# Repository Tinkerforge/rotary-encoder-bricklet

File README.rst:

Rotary Encoder Bricklet
=======================

This repository contains the firmware source code and the hardware design
files. The documentation generator configs can be found at
https://github.com/Tinkerforge/generators

Repository Content
------------------

software/:
 * examples/: Examples for all supported languages
 * build/: Compiled files
 * src/: Source code of firmware
 * Makefile: Makefile to build project

hardware/:
 * Contains KiCad project files and additionally schematics as PDF

datasheets/:
 * Contains datasheets for sensors and complex ICs that are used

Hardware
--------

The hardware is designed with the open source EDA Suite KiCad
(http://www.kicad.org). Before you are able to open the files,
you have to install the Tinkerforge kicad-libraries
(https://github.com/Tinkerforge/kicad-libraries). You can either clone
them directly in hardware/ or clone them in a separate folder and
symlink them into hardware/
(ln -s kicad_path/kicad-libraries project_path/hardware). After that you
can open the .pro file in hardware/ with KiCad and from there view and
modify the schematics and the PCB layout.

Software
--------

If you want to do your own Brick/Bricklet firmware development we highly
recommend that you use our build environment setup script and read the
tutorial (https://www.tinkerforge.com/en/doc/Tutorials/Tutorial_Build_Environment/Tutorial.html).

To compile the C code we recommend you to install the newest GNU Arm Embedded
Toolchain (https://launchpad.net/gcc-arm-embedded/+download).
You also need to install bricklib (https://github.com/Tinkerforge/bricklib)
and brickletlib (https://github.com/Tinkerforge/brickletlib).

You can either clone it directly in software/src/ or clone it in a
separate folder and symlink it into software/src/
(ln -s bricklib_path/bricklib project_path/software/src/ and
ln -s brickletlib_path/brickletlib project_path/software/src/).
Finally make sure to have CMake installed
(http://www.cmake.org/cmake/resources/software.html).

After that you can build the firmware by invoking make in software/.
The firmware (.bin) can then be found in software/build/ and uploaded
with brickv (click button "Flashing" on start screen).

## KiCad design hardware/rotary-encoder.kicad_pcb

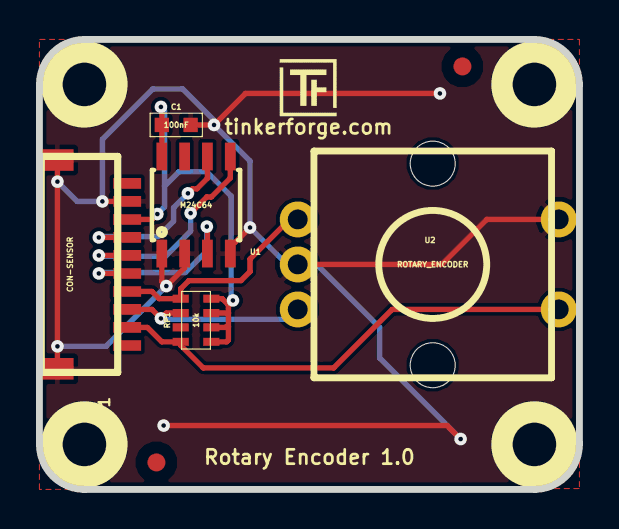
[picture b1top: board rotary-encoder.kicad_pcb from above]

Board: 2 copper layers, 30.0 x 25.0 mm, 13 parts (0 on the bottom side), 8 nets.

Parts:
C1: 100nF; 0603
Fiducial_Mark: VAL**; Fiducial_Mark
Fiducial_Mark#2: VAL**; Fiducial_Mark
P1: CON-SENSOR
RP1: 10k; 4X0603
U1: M24C64; SOIC8
U2: ROTARY_ENCODER
U3, U4, U5, U6: DRILL; DRILL_NP
VAL: WEEE_7mm
VAL#2: CE_5mm

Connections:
GND: C1.2, P1.2, P1.EP, U1.1, U1.2, U1.4, U2.C, U2.SW2
unnamed: P1.6, U1.3
unnamed: P1.9, RP1.1, U2.SW1
unnamed: P1.8, RP1.3, U2.B
unnamed: P1.7, RP1.4, U2.A
unnamed: P1.4, U1.6
unnamed: P1.5, U1.5
VCC: C1.1, P1.3, RP1.5, RP1.6, RP1.7, RP1.8, U1.8

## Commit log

2013-08-20 Initial commit of Rotary Encoder Bricklet (actual counting still missing in firmware)
2013-08-20 Add count reset functionality
2013-08-21 Add count calculation API for button pressed/released
2013-08-21 Add encoder datasheet
2013-08-21 windows: Don't trigger a build in generate_makefile.bat
    Also use normal make instead of a special named one.
2013-09-13 Add examples for Rotary Encoder Bricklet
2013-09-13 Fix variable name
2013-09-13 Fix variable name in java examples
2013-10-15 add hardware files
2013-10-18 Fix name to fit naming convention
2013-12-19 Fix wrong length for GetDebounce packet (through brickletlib)
2014-01-06 Add static assert for BrickContext size
2014-01-10 Add Perl examples
2014-01-15 php: Use const for constant values
2014-02-07 Add Mathematica examples
2014-02-10 perl: fixed namespace
2014-02-11 javascript: add examples
2014-02-18 javascript: examples fixed
2014-02-20 javascript: add html examples
2014-02-24 javascript: port 4280, startExample()
2014-02-28 javascript: Break long lines and cleanup whitespace
2014-03-05 Fix typo
2014-03-05 Add LabVIEW examples
2014-03-06 labview: Add examples in LV2010 format
2014-03-27 matlab: add examples
2014-03-28 perl: Fix warning
2014-04-02 java: Unify constants style
2014-04-02 perl: Unify print style
2014-04-17 matlab: Adapt examples to new callback style
2014-04-17 matlab: Add parentheses to make pygments happy
2014-07-15 java: Replace System.console() usage with an Eclipse compatible pattern
2014-12-02 Use ReadLine instead of ReadKey for C# example
2015-02-13 vbnet: Use ReadLine instead of ReadKey
    Because ReadKey doesn't work with a pipe as stdin on the RED Brick.
2015-03-02 windows: Stop cmake from searching for mingw32-make.exe
    Using MinGW Makefiles as generator makes cmake search for mingw32-make.exe
    which might not be installed because GnuWin32's make.exe is used instead.
2015-04-09 c: Whitespace
2015-06-24 javascript: Clean up output creation
2015-07-25 Make JavaScript browser example textarea readonly
2015-07-27 Cleanup C/C++, C#, Java, Python and Ruby examples
2015-07-28 Whitespace
2015-07-29 Reformat changelog
2015-07-30 Unify comments in examples
2015-08-07 Use full device class name in Python examples
2015-08-12 Fix minor warnings in C/C++ examples
2015-08-14 Cleanup Delphi examples
2015-08-18 Cleanup VB.NET examples
2015-08-19 Cleanup Perl examples
2015-08-21 Use shorter print statement in Perl example
2015-09-09 Duplicate cmake call to fix bug during cmake creation
2015-09-30 Generator based example cleanup
2015-11-12 matlab: Fix callback handling for R2014a
    http://undocumentedmatlab.com/blog/matlab-callbacks-for-java-events-in-r2014a
2015-11-25 Include date and commit into changelog
2016-04-25 Fix inverted is_pressed return value
2016-04-25 Add changelog commit after the fact
2016-05-18 c: Add missing device destroy call
2016-07-01 Make the change UID comment more explicit
2017-04-13 csharp: Adapt example
2017-06-02 octave: Use javaObject instead of deprecated java_new
2017-11-30 Update examples from generator
2017-12-07 mathematica: Also generate .nb files
2018-02-19 javascript: Close div tag correctly
2018-02-20 Cleanup KiCad libraries config
    Ensure LibDir=kicad-libraries and LibName1=tinkerforge.
    Remove special library.
2018-05-11 Rename files
2018-05-24 perl: Use strict in examples
2018-07-11 Add Makefile with docker support
2018-07-11 Remove obsolete generate_makefile scripts
2018-07-11 Update directory structure and build instructions
2018-11-06 Add rust examples
2018-11-07 rust: Accept host names for ip connection, fix naming inconsistencies
2018-11-07 rust: Rename callback receivers.
2018-12-14 Add go examples.
2018-12-18 go: Change import path.
2018-12-18 go: Change import path again.
2018-12-20 rust: Reformat examples.
2019-01-24 mqtt: Add examples.
2019-01-24 mqtt: Fix example header.
2019-01-24 mqtt: Remove executable bit in example permissions.
2019-01-24 go: Minor example fixes.
2019-01-24 mqtt: Minor example fixes.
2019-03-25 mqtt: Fix example whitespace.
2019-03-28 mqtt: Fix whitespace.
2019-08-22 c: Adapt to bindings changes
2020-01-13 examples: Use python3 input instead of python2 raw_input.
2020-01-13 examples: mqtt: Remove trailing whitespace.
2021-10-25 Update KiCad link
    https://www.kicad.org/blog/2021/10/Avoid-links-to-former-kicad-domain/
2022-05-10 go: Fix format string
2022-07-06 Add license files.

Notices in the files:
hardware/rotary-encoder.kicad_pcb:
Licensed under CERN OHL v.1.1
Copyright (©) 2013, B.Nordmeyer
Copyright Tinkerforge GmbH 2013.
This documentation describes Open Hardware and is licensed under the
CERN OHL v. 1.1.
